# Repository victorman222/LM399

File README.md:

LM399/ADR1399 reference

A 10 V voltage reference using LM399/ADR1399 IC.

- General features:
  - Protected from input reverse polarity and overvoltage up to 60 V
  - Protected from output short circuit and backfeed up to 30 V 
  - Extensive RLC filter on the input and linear regulator relaxes power supply requirements  
  - Common mode filters featuring guard connection make reference resilient from common mode currents (EMI)
- Precision features:
  - Uses bootstrap scheme where output opamp is powered by the output voltage, improving PSRR (DC PSRR 200nV/V without linear regulator)
  - Main divider uses 3 resistors (2 in parallel), so it is possible to build with identical value resistors
  - Supports 150 and 200 mil radial and 1206 resistors for the divider
  - Pads for trimming with fixed through hole resistors
  - Trimming with potentiometer uses scheme that can reduce the trim range to single PPM without high value resistors
  - Trimpot is used in potentiometer (ratio) mode which has better TC and stability
  - Supports most trimpots with 100mil inline lead spacing, also supports SP5-35 fine/coarse potentiometer
  - Provides low impedance to both of the opamp inputs such that chopper amps can be used without extra current noise
  - ADR1399 uses 10u/1R snubber that makes it more stable than usual 1u/5R (stable here as in control theory, not PPMs)
 
- Changes from REV A:
  - 6 layer board with inner layers for Kelvin output connections
  - Changed location of LM399, so now all heat sources are on the left, moved other heat sources away from output
  - New trim scheme and new huge trimpot footprint
  - Added 7815 regulator
  - SMD pass transistor, heat disipated to case through mounting hole and radiation
  - Added circuit that turns off pass transistor periodically if output voltage is low to reset thyristor when backfeed event has ended
  - Increased output load resistor value, because the lm399 heater already provides enough minimal load
  - BOM optimization, decreased amount of different values
  - Added guard traces around inverting node
  - Increased output capacitance such that opamp should be stable without extra frequency compensation
  - Increased R15 to improve AC PSRR, this is possible because new BJT has higher current gain
  - New opamp offset trim scheme, seems sound in theory but not much info on it
  - Tantalum caps everywhere other than the very big cap
  - Added C28 "feedforward" capacitor which makes circuit gain unity at high frequency, it also removes effect of inverting node capacitance to ground on stability and gives a low impedance path for charge injection of chopper amps inverting input
  - Decreased R12 value since it was reducing DC open loop gain (downside is that now it makes less of a "zero" with C12?)
  - Changed adr1399 snubber from 1u/5R to 10u/1R after doing some experiments with different cap values
  - Added two mounting holes, finally we can have 4 (although the case still comes with only two screws :/ )
  - The board is now very double sided load, most precision stuff is on the bottom

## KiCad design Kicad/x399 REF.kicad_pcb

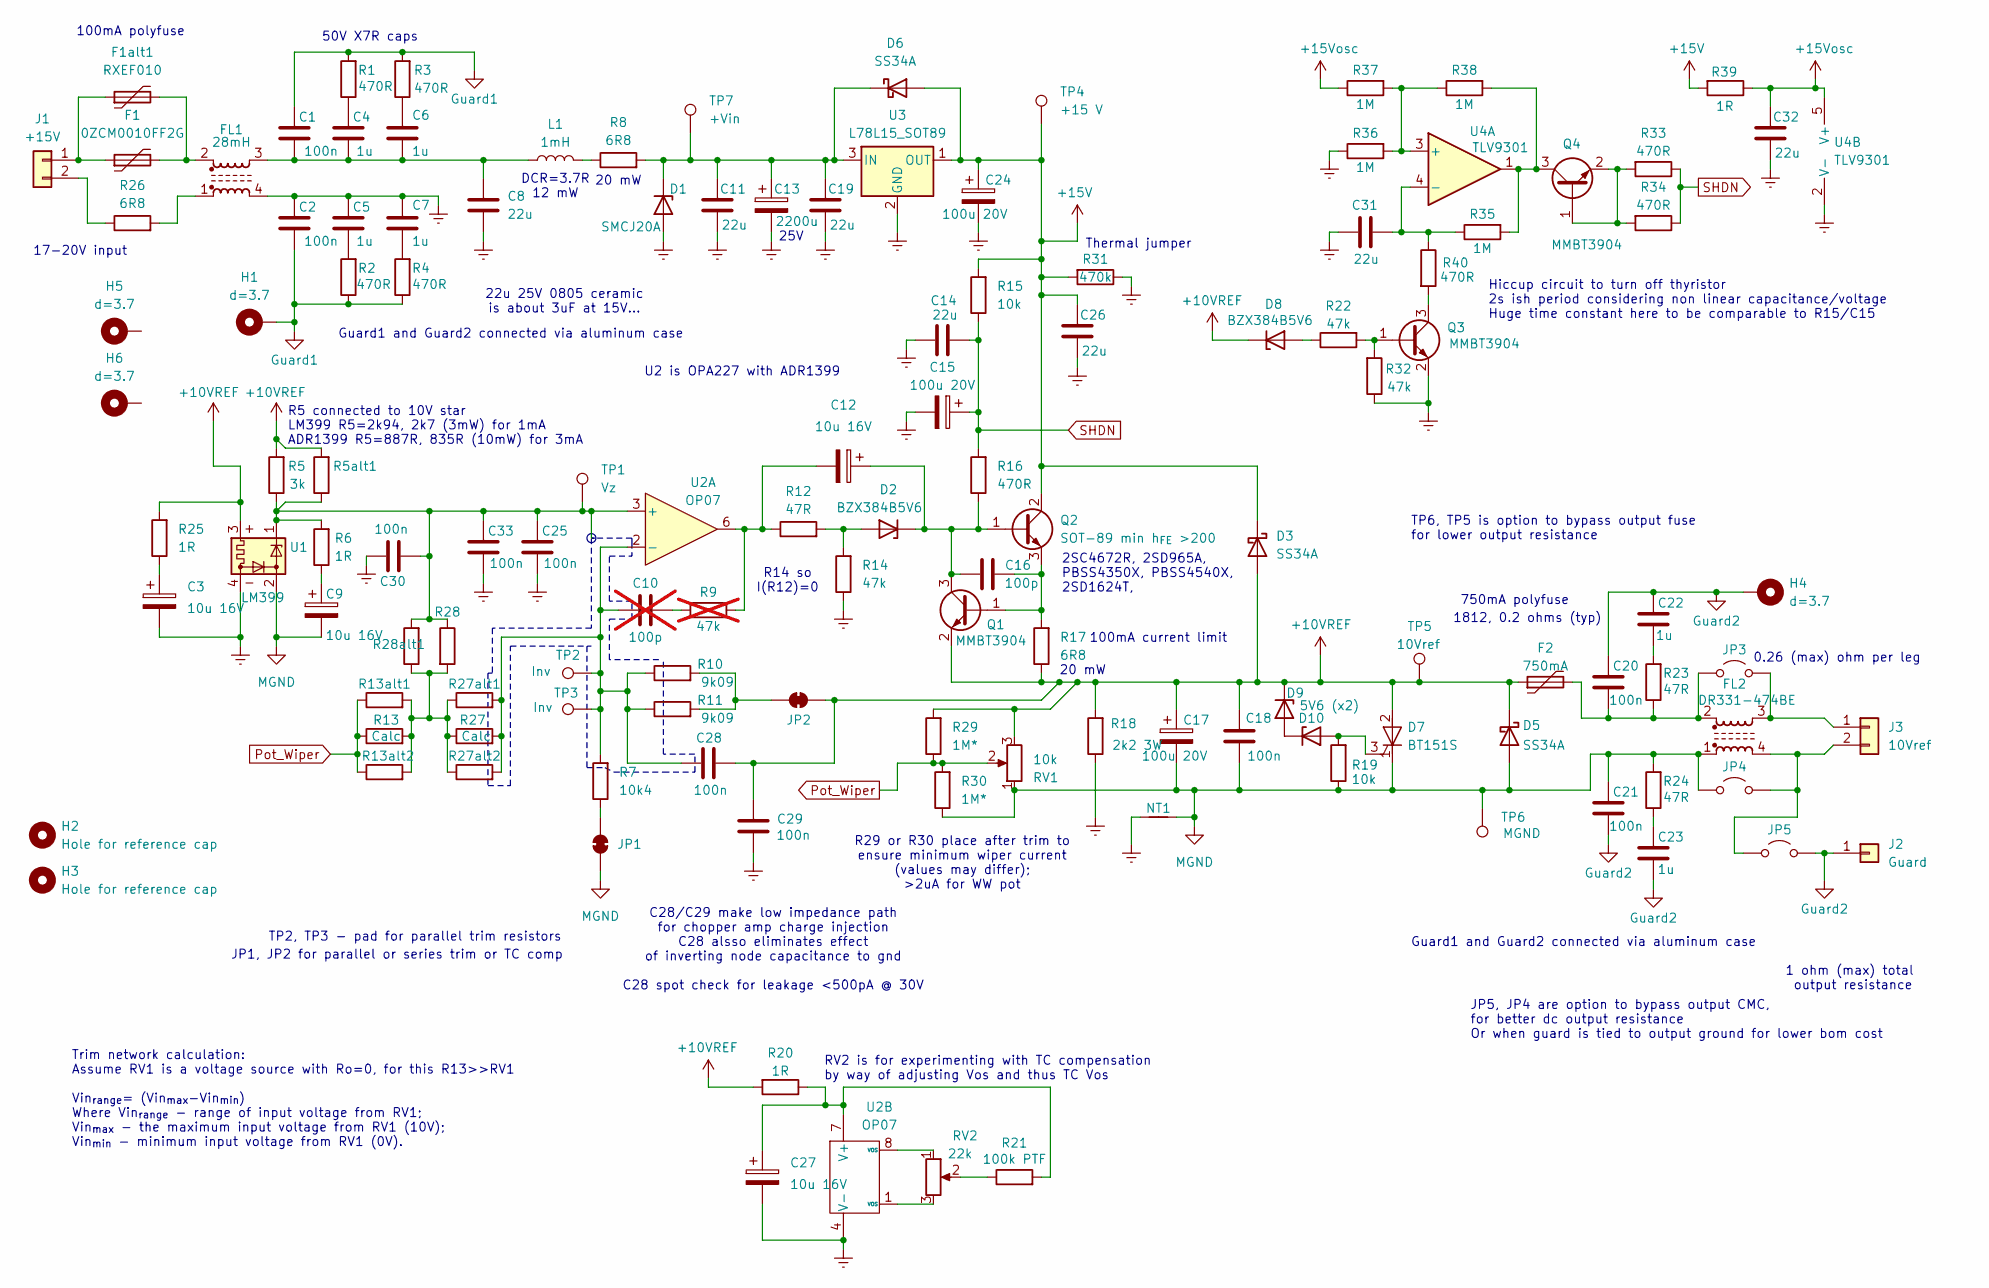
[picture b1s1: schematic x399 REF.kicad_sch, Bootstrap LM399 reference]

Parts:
C1, C2: 100n; C_0805_2012Metric_Pad1.18x1.45mm_HandSolder
C3, C9, C12, C27: 10u 16V; CP_EIA-3216-18_Kemet-A_HandSolder
C4, C5, C6, C7: 1u; C_0805_2012Metric_Pad1.18x1.45mm_HandSolder
C8, C11, C14, C19, C26, C31, C32: 22u; C_0805_2012Metric_Pad1.18x1.45mm_HandSolder
C10: 100p; C_0805_2012Metric_Pad1.18x1.45mm_HandSolder; not fitted
C13: 2200u; CP_Radial_D13.0mm_P5.00mm
C15, C17, C24: 100u 20V; CP_EIA-7343-31_Kemet-D_HandSolder
C16: 100p; C_0805_2012Metric_Pad1.18x1.45mm_HandSolder
C18, C20, C21, C25, C28, C29, C30, C33: 100n; C_1206_3216Metric_Pad1.33x1.80mm_HandSolder
C22, C23: 1u; C_Rect_L7.2mm_W5mm_P5.00mm_FKS2_FKP2_MKS2_MKP2
D1: SMCJ20A; D_SMB-SMC_Universal_Handsoldering
D2, D8, D9, D10: BZX384B5V6; D_SOD-323_HandSoldering
D3, D6: SS34A; D_SMA
D5: SS34A; D_SMA_Handsoldering
D7: BT151S; TO-252-2
F1: 0ZCM0010FF2G; R_0603_1608Metric_Pad0.98x0.95mm_HandSolder
F1alt1: RXEF010
F2: 750mA; R_1812_4532Metric_Pad1.30x3.40mm_HandSolder
FL1: 28mH; Universal line filter
FL2: DR331-474BE; L_CommonMode_Bourns_DR331_Handsolder
H1, H4, H5, H6: d=3.7; MountingHole_3.7mm_Pad_Via_6.7mm diameter
H2, H3: Hole for reference cap; MountingHole_3.2mm_M3
J1: +15V; SolderWire-0.1sqmm_1x02_P3.6mm_D0.4mm_OD1mm_Relief
J2: Guard; SolderWire-0.127sqmm_1x01_D0.48mm_OD1mm_Relief
J3: 10Vref; SolderWire-0.127sqmm_1x02_P3.7mm_D0.48mm_OD1mm_Relief
JP1, JP2: Joined holes D=1.8 Dh=0.9 P=3mm
JP3, JP4, JP5: TestPoint_2Pads_Pitch2.54mm_Drill0.8mm
L1: 1mH; L_7.3x7.3_H4.5_Handsoldering
NT1: NetTie-2_SMD_Pad2.0mm
Q1, Q3, Q4: MMBT3904; SOT-23_Handsoldering
Q2: SOT-89 min h_{FE} >200; SOT-89-3_Handsoldering
R1, R2, R3, R4, R16, R33, R34, R40: 470R; R_0603_1608Metric_Pad0.98x0.95mm_HandSolder
R5: 3k; R_Axial_DIN0309_L9.0mm_D3.2mm_P12.70mm_Horizontal
R5alt1: smd; R_1206_3216Metric_Pad1.30x1.75mm_HandSolder
R6, R20, R25, R39: 1R; R_0603_1608Metric_Pad0.98x0.95mm_HandSolder
R7: 10k4; S5-61+vishay(150mil)+smd1206
R8, R17, R26: 6R8; R_1206_3216Metric_Pad1.30x1.75mm_HandSolder
R9: 47k; R_0603_1608Metric_Pad0.98x0.95mm_HandSolder; not fitted
R10, R11: 9k09; S5-61+vishay(150mil)+smd1206
R12, R23, R24: 47R; R_0603_1608Metric_Pad0.98x0.95mm_HandSolder
R13, R27: Calc; R_Axial_DIN0918_L18.0mm_D9.0mm_P22.86mm_Horizontal
R13alt1, R27alt1, R28: 0.6W tht; R_Axial_DIN0309_L9.0mm_D3.2mm_P12.70mm_Horizontal
R13alt2, R27alt2, R28alt1: 1206 smd; R_1206_3216Metric_Pad1.30x1.75mm_HandSolder
R14, R22, R32: 47k; R_0603_1608Metric_Pad0.98x0.95mm_HandSolder
R15, R19: 10k; R_0603_1608Metric_Pad0.98x0.95mm_HandSolder
R18: 2k2 3W; R_Axial_DIN0617_L17.0mm_D6.0mm_P5.08mm_Vertical
R21: 100k PTF; R_0805_2012Metric_Pad1.20x1.40mm_HandSolder
R29, R30: 1M*; R_0603_1608Metric_Pad0.98x0.95mm_HandSolder
R31: 470k; R_1210_3225Metric_Pad1.30x2.65mm_HandSolder
R35, R36, R37, R38: 1M; R_0603_1608Metric_Pad0.98x0.95mm_HandSolder
RV1: 10k; SP5-35+SP5-2VB
RV2: 22k; Potentiometer_Soviet_SP5-2VB
TP1: Vz; TestPoint_Loop_D2.50mm_Drill1.0mm
TP2, TP3: Inv; TestPoint_THTPad_D1.8mm_Drill0.9mm
TP4: +15 V; TestPoint_Loop_D2.50mm_Drill1.0mm
TP5: 10Vref; TestPoint_Loop_D2.50mm_Drill1.0mm
TP6: MGND; TestPoint_Loop_D2.50mm_Drill1.0mm
TP7: +Vin; TestPoint_Loop_D2.50mm_Drill1.0mm
U1: LM399; Analog_TO-46-4_ThermalShield
U2: OP07; DIP-8_W7.62mm_W_soic_under
U3: L78L15_SOT89; SOT-89-3
U4: TLV9301; SOT-23-5_HandSoldering

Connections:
+10VREF: C17.1, C18.1, C28.2, C29.2, D3.2 (A), D5.1 (K), D7.2 (A), D8.1 (K), D9.1 (K), F2.1, JP2.2 (B), Q1.2 (E), R5.2, R5alt1.2, R17.1, R18.1, R20.2, R25.2, R29.2, RV1.3, TP5.1 (1_1), U1.3
+15V: C24.1, C26.1, D3.1 (K), D6.2 (A), Q2.2 (C), R15.2, R31.2, R39.2, TP4.1 (1_1), U3.1 (OUT)
+15Vosc: C32.1, R37.1, R39.1, U4.5 (V+)
Earth: C2.1, C3.2, C5.1, C7.1, C8.2, C11.2, C13.2, C14.1, C15.2, C19.2, C24.2, C25.2, C26.2, C27.2, C29.1, C30.2, C31.1, C32.2, C33.2, D1.2 (A), FL1.4, NT1.1, Q3.2 (E), R14.1, R18.2, R31.1, R32.1, R36.1, U1.4, U2.4 (V-), U3.2 (GND), U4.2 (V-)
Guard1: C1.1, C2.2, H1.1 (1_1), R1.2, R2.1, R3.2, R4.1
Guard2: C20.1, C21.2, C22.1, C23.2, H4.1 (1_1), J2.1 (Pin_1_1), JP5.2 (B)
MGND: C9.2, C17.2, C18.2, C21.1, D5.2 (A), D7.1 (K), FL2.1, JP1.1 (A), JP4.1 (A), NT1.2, R19.1, R24.2, R30.1, RV1.1, TP6.1 (1_1), U1.2
unnamed: C1.2, C4.2, C6.2, C8.1, FL1.3, L1.1
unnamed: C3.1, R25.1
unnamed: C4.1, R1.1
unnamed: C5.2, R2.2
unnamed: C6.1, R3.1
unnamed: C7.2, R4.2
unnamed: C9.1, R6.1
unnamed: C10.2, R9.1
unnamed: C12.2, R9.2, R12.1, U2.6
unnamed: C22.2, R23.2
unnamed: C23.1, R24.1
unnamed: C11.1, C13.1, C19.1, D1.1 (K), D6.1 (K), R8.2, TP7.1 (1_1), U3.3 (IN)
unnamed: D2.2 (A), R12.2, R14.2
unnamed: C12.1, C16.1, D2.1 (K), Q1.3 (C), Q2.1 (B), R16.1
unnamed: D8.2 (A), R22.1
unnamed: D7.3 (G), D10.2 (A), R19.2
unnamed: D9.2 (A), D10.1 (K)
unnamed: F1.2, F1alt1.2, FL1.2
unnamed: FL1.1, R26.2
unnamed: F1.1, F1alt1.1, J1.1
unnamed: J1.2, R26.1
unnamed: FL2.3, J3.1, JP3.2 (B)
unnamed: FL2.4, J3.2, JP4.2 (B), JP5.1 (A)
unnamed: JP1.2 (B), R7.1
unnamed: JP2.1 (A), R10.2, R11.2
unnamed: C20.2, F2.2, FL2.2, JP3.1 (A), R23.1
unnamed: L1.2, R8.1
unnamed: C16.2, Q1.1 (B), Q2.3 (E), R17.2
unnamed: Q3.1 (B), R22.2, R32.2
unnamed: Q3.3 (C), R40.2
unnamed: Q4.1 (B), Q4.2 (E), R33.2, R34.2
unnamed: Q4.3 (C), R35.2, R38.2, U4.1
unnamed: R13.2, R13alt1.2, R13alt2.2, R27.1, R27alt1.1, R27alt2.1, R28.2, R28alt1.1
unnamed: R21.1, RV2.2
unnamed: RV2.1, U2.8 (VOS)
unnamed: RV2.3, U2.1 (VOS)
unnamed: C25.1, C30.1, C33.1, R5.1, R5alt1.1, R6.2, R28.1, R28alt1.2, TP1.1 (1_1), U1.1, U2.3 (+)
unnamed: C10.1, C28.1, R7.2, R10.1, R11.1, R27.2, R27alt1.2, R27alt2.2, TP2.1 (1_1), TP3.1 (1_1), U2.2 (-)
unnamed: C27.1, R20.1, R21.2, U2.7 (V+)
unnamed: R36.2, R37.2, R38.1, U4.3 (+)
unnamed: C31.2, R35.1, R40.1, U4.4 (-)
Pot_Wiper: R13.1, R13alt1.1, R13alt2.1, R29.1, R30.2, RV1.2
SHDN: C14.2, C15.1, R15.1, R16.2, R33.1, R34.1

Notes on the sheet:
100mA polyfuse
20 mW
Guard1 and Guard2 connected via aluminum case
LM399 R5=2k94, 2k7 (3mW) for 1mA ADR1399 R5=887R, 835R (10mW) for 3mA
TP2, TP3 - pad for parallel trim resistors
R29 or R30 place after trim to ensure minimum wiper current (values may differ); >2uA for WW pot
1812, 0.2 ohms (typ)
100mA current limit
50V X7R caps
750mA polyfuse
TP6, TP5 is option to bypass output fuse for lower output resistance
22u 25V 0805 ceramic is about 3uF at 15V...
1 ohm (max) total output resistance
Thermal jumper
Trim network calculation: Assume RV1 is a voltage source with Ro=0, for this R13>>RV1 Vin_{range}= (Vin_{max}-Vin_{min}) Where Vin_{range} - range of input voltage from RV1; Vin_{max} - the maximum input voltage from RV1 (10V); Vin_{min} - minimum input voltage from RV1 (0V).
Hiccup circuit to turn off thyristor 2s ish period considering non linear capacitance/voltage Huge time constant here to be comparable to R15/C15
C28/C29 make low impedance path for chopper amp charge injection C28 alsso eliminates effect of inverting node capacitance to gnd C28 spot check for leakage <500pA @ 30V
DCR=3.7R 12 mW
RV2 is for experimenting with TC compensation by way of adjusting Vos and thus TC Vos
25V
R14 so I(R12)=0
2SC4672R, 2SD965A, PBSS4350X, PBSS4540X, 2SD1624T,
U2 is OPA227 with ADR1399
0.26 (max) ohm per leg
JP1, JP2 for parallel or series trim or TC comp
17-20V input
JP5, JP4 are option to bypass output CMC, for better dc output resistance Or when guard is tied to output ground for lower bom cost
R5 connected to 10V star

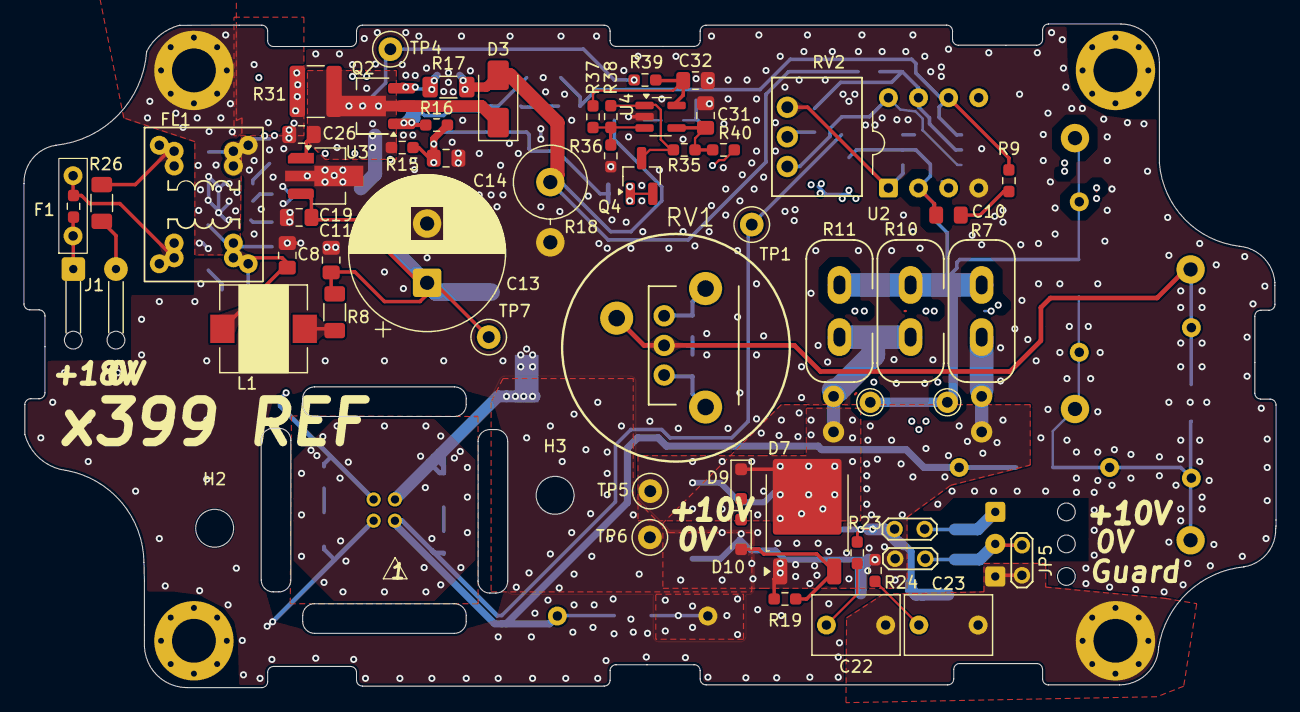
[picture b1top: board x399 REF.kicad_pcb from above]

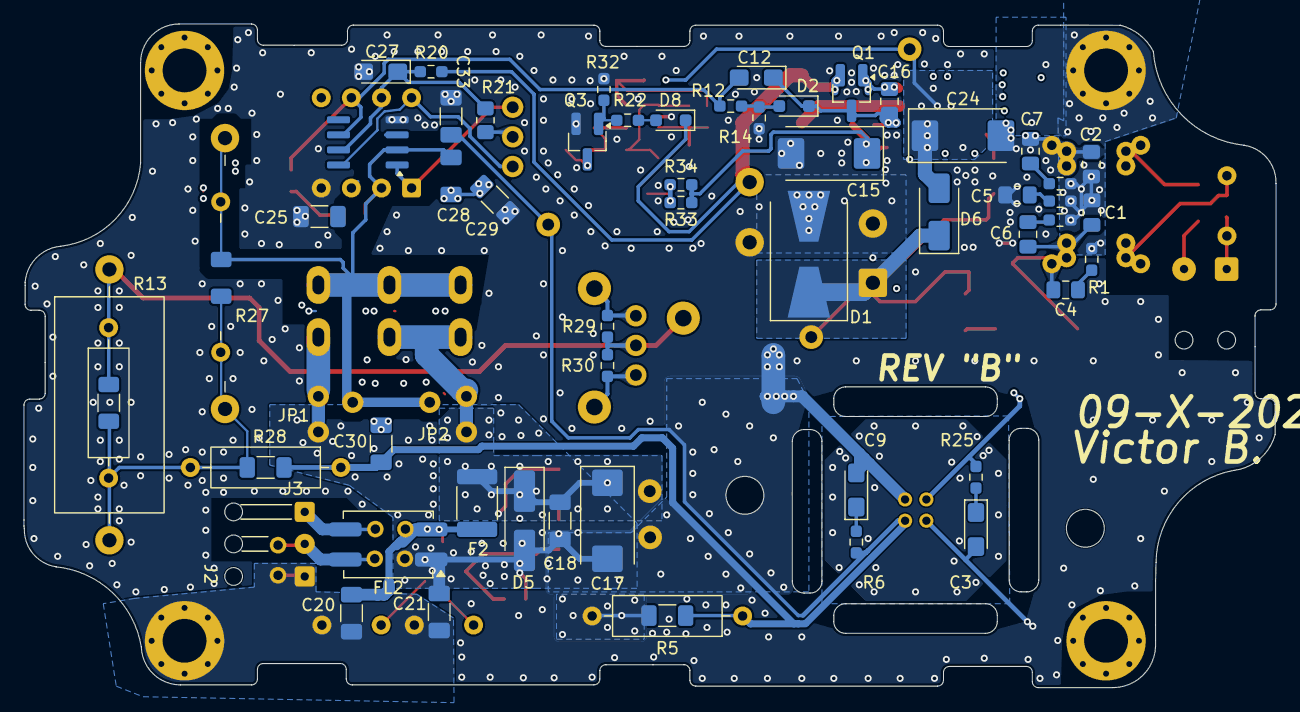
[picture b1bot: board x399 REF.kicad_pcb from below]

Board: 6 copper layers, 105.7 x 56.0 mm, 126 parts (62 on the bottom side), 50 nets.

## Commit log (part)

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2025-07-10 Create delete
2025-07-11 Board revision
    Rotated LM399 to have sensitive to TEMF pins (1,2) perpendicular to thermal gradient
2025-07-11 Board revision
    Rotate transistor so it can be mounted to enclosure for heatsinking
2025-07-11 Update images to latest board ver
2025-07-11 Update PCB drawings
2025-07-11 Replace DIP8-400mil wide footprint to standard 300mil
2025-07-21 Add files via upload
    Removed slots in middle of board, increased size of zener return trace and voltage divider traces
2025-07-25 Add files via upload
    Replaced guard 2 1u film capacitors for more accessible ones, improved thermal design on output
2025-07-25 Add files via upload
    Replaced guard2 1u film capacitors for more accessible ones, improved thermal design on output
